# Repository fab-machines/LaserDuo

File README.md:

<div align="center"><h1 style="font-family: courier;" align="center">LaserDuo</h1></div>

<div align="center"></div>
<div align="center"><i>Open Source Dual Laser Cutter</i></div>

Premises
--
We dream in a future of freedom, where open source hardware and [Fab Labs](https://fablabs.io/) enable people to fully understand how to make things they need, and where decentralized local production is customized to impact the surrounding community. Believing that empowering the user with knowledge about how to make machines, LaserDuo wants to give to the world a powerful open source tool, to lasercut (almost) any material. And, together with [BigFDM](https://github.com/fab-machines/BigFDM), this is one of the first steps in developing other machines sharing the same philosophy.

LaserDuo
--
LaserDuo is an open source laser cutter having two different laser sources. Using a 130W CO2 and a 75W YAG lasers, LaserDuo can work with a wide range of materials such as wood and metals.

Taking advantage of what we have learned in [Fab Academy](https://fabacademy.org/), LaserDuo has been developed using standard [Fab Lab equipment](https://docs.google.com/spreadsheets/d/1U-jcBWOJEjBT5A0N84IUubtcHKMEMtndQPLCkZCkVsU/pub?single=true&gid=0&output=html) and [techniques](http://fab.academany.org/2019/schedule.html) plus a membrane press machine to bend the aluminum parts. LaserDuo was developed at [Fab Lab Kamp-Linfort](https://fablab.hochschule-rhein-waal.de/about-us) by Daniele Ingrassia. Reversing the consumer process, where knowledge and building of machines stays inside a black box managed by companies, LaserDuo brings the advantages of an open source development:

- full awareness about how the machine works
- reproducible design
- possibility to customize the machine and/or to build new ones
- built as much as possible with local materials
- local self-fixing and self-production of the machine parts
- community can use and improve the design
- cheap alternative to large scale 3D printers
- use LaserDuo as tool to produce other open source machines

Developed and built in a Fab Lab as multipurpose machine, LaserDuo allows to access the laser cutting technology at lower price in comparison to similar machines available on the market. Especially considering the possibility to work with metals. The open source design allows the user to fix the machine by himself, and to be aware of the process in a way that he can use it to reproduce the machine or parts for it. Being a challenging project from several aspects, such as size of the working area, Z-axis, speed, resolution and the dual laser, it also offers additional features like an integrated PC to control the machine and launch jobs, air assist, solid aluminum bodywork.

**LaserDuo specifications**:

- **1500mm x 1000mm** cutting area
- **500mm Z axis**
- **dual laser source**
- **130W CO2** laser
- **75W YAG** laser
- **800mm/s** maximum speed
- **Nema 24** stepper motors
- **air assist**
- integrated **tablet** for machine control
- **1000DPI or 0.0254mm** resolution
- open source **satshakit biards** for machine control
- dedicated sealed **exhaust chamber**
- **certified laser protective window**
- **safety features** emergency switch, windows interlock
- **fully enclosed 100% aluminum housing**
- dimensions: 2250mm x 2100mm x 1500mm

Machine design
--

The overall project has been designed by following a bottom-up approach, where the first step was to make a single machine axis. Every step focused on developing a single machine section, designing and constraining it according to the previous steps and machine features. You can consider this like being almost blind about the next step, until the current one has been assessed as able to work properly. It is therefore for me still astonishing the complete transition to the final machine look, generated by the chaining of the dependencies of several design steps.

X and Y stages
--

As many other laser cutters, also the stages of LaserDuo have been designed to be light and fast. Linear rails together with CNC milled POM and aluminium profiles have been used. To be noticed this step took a lot time, especially during the assembly to ensure the correct squareness of the frame and the perpendicularity of the axis. Both X and Y axis are moved by Nema 24 motors.

Z Axis
--

I always had something to do with lasers having Z axis, before learning that some chinese laser don’t have it. Therefore for me was quite normal to consider to have it. However I had a long reasoning about the justification of the extra costs vs the possible benefits. Then I had the idea to eventually make a 3D printer as a possible upgrade for LaserDuo, while considering that I still needed to find a solution to properly take the focus by moving the lens up and down. That convinced me to add it. The Z axis consist of 4 lead-screws, supported by ball bearings and moved a closed loop belt. The frame has been designed in a way to fit the Z axis inside and to have the machine high enough to be on wheels.

Inner enclousure
--

Designed on purpose to shield the laser focusing area and to make the fumes having a certain flow towards the exhaust system, the inner enclosure consists of CNC milled 1.5mm anodized aluminium sheets. There are vents both in the front and the back, allowing fresh air to come from outside, cool the cutting area, and be exhausted through a sealed box.

<br><br><br>

Housing
--

The housing completely encloses the machine, while keeping 3 exhaust tubes in the back and some ultrathin air intakes. The design uses curves to allow the feet to fit when coming close to the machine, and as well to save material. Laser, exhaust, electronics and optics are located in different areas, accessible by removing a specific panel for maintenance.

<br><br><br>

<br><br><br>

Electronics
--
The electronics of LaserDuo consists of a set of fabbable electronics, derived from the original **[satshakit](https://github.com/satshakit)** board and **[satstep](https://github.com/satstep)** stepper drivers. Following the used boards and their role in LaserDuo.<br>

**[satshakit-mega](https://github.com/fab-machines/LaserDuo/tree/master/electronics/satshakit-mega)**

Based on the [ATMega2560](https://www.microchip.com/wwwproducts/en/ATmega2560), this board provides the necessary microcontroller hardware to manage LaserDuo dual laser logic and additional sensors. Furthermore integrates an USB-to-Serial converter and USB port. Developed as general purpose board, not all the pins will be used. In the future this board will be a custom made solution for LaserDuo. Link to the original [repo](https://github.com/satshakit/satshakit-mega).

---------

**[satshakit-grbl](https://github.com/fab-machines/LaserDuo/tree/master/electronics/satshakit-grbl)**

Used to run **[GRBL 1.1](https://github.com/gnea/grbl)** in laser mode, satshakit-grbl is based on the ATMega328p and as well integrates nise filtering for the endstops. Link to the original repo [satshakit-grbl](https://github.com/satshakit/satshakit-grbl)

---------

**[satstep6600](https://github.com/fab-machines/LaserDuo/tree/master/electronics/satstep6600)**

Proved to have a robust design by being used in **[LaserDuo](http://laserduo.com/)** for more than a year, the satstep6600 is the stepper driver used to move the NEMA 24. Based on the Toshiba [TB6600HG](http://www.massmind.org/images/massmind/TB6600HG_datasheet.pdf) it can give up to 4.5A per coil to a single motor, whereas the NEMA 24 used will take a maximum of 4A. Link to the original [repo](https://github.com/satstep/satstep6600).

---------

Summary of the needed boards:

- 1 x satshakit-mega
- 1 x satshakit-grbl
- 3 x satstep6600

To power all this electronics, and to control the laser sources the following additional electronics is needed:

- 15A 24V power supply
- CO2 power supply (~40KV)
- YAG power supply

Make your own LaserDuo
--

LaserDuo is made by using a mix of fabricated and ready-made parts. The ready-made parts are selected to be as common/standard as possible, to make the sourcing of them easy in many countries. For both the raw materials needed for the fabricated parts, and the ready-made parts, refer to the Bill-of-Material for details: **[LaserDuo BOM](https://github.com/fab-machines/LaserDuo/raw/master/docs/LaserDuo%20BOM.pdf)**

The fabrication of the parts mainly relays on standard [Fab Lab equipment](https://docs.google.com/spreadsheets/d/1U-jcBWOJEjBT5A0N84IUubtcHKMEMtndQPLCkZCkVsU/pub?single=true&gid=0&output=html) plus a membrane press machine. Below a list of the required tools and machines:

- C02 laser cutter:
 - able to cut 8mm POM
 - needed for POM parts and holders
- large format wood CNC machine:
 - ShopBot or similar, size 2500x1250mm
 - to machine the POM parts (X, Y, Z, axis)
 - to machine the Aluminum parts (inner enclousure, housing)
- 3D printer:
 - a medium sized one (50x50x50cm)
 - to print the inner housing parts 
- Desktop format CNC machine:
 - Roland MDX50/MDX20/SRM20 or similar small machine (as well the cheap chinese ones)
 - to produce the required PCBs
- standard set of tools:
 - spanner key set
 - hex key set
 - DIN 875
 - calipers
 - rulers
 - screwdriver set
 - player set (grabber/cutter etc..)
 - clamps
 - rubber hummers
- membrane press machine
 - to bend the housing parts  

Both fabricated and ready-made parts have been modeled inside the **[LaserDuo Fusion 360 3D model](https://github.com/fab-machines/LaserDuo/raw/master/cad/LaserDuo.f3d)**. Using Fusion is possible to export/prepare the parts for production in the following ways:

- right click save as STL, on a body that needs to be 3D printed
- use the built-in Fusion CAM processor for the machined parts
- project on a surface, and then right click export as DXF, for laser cutting
 
For more details about the tools and once you have all the fabricated and ready-made parts parts available, refer to the for step-by-step assembly instructions and tips: **[LaserDuo Building Manual](https://github.com/fab-machines/LaserDuo/raw/master/docs/LaserDuo%20building%20manual.pdf)** 

LaserDuo requires different fabbable PCBs to work. Below the download links for the eagle files that you use to fabricate them:

- **[satshakit-mega schematic](https://raw.githubusercontent.com/fab-machines/LaserDuo/master/electronics/satshakit-mega/satshakit-mega.sch)**, **[satshakit-mega board](https://raw.githubusercontent.com/fab-machines/LaserDuo/master/electronics/satshakit-mega/satshakit-mega.brd)**

- **[satstep6600 schematic](https://github.com/fab-machines/LaserDuo/raw/master/electronics/satstep6600/satstep6600.sch)**, **[satstep6600 board](https://github.com/fab-machines/LaserDuo/raw/master/electronics/satstep6600/satstep6600.brd)**

- **[satshakit-grbl schematic](https://github.com/fab-machines/LaserDuo/raw/master/electronics/satshakit-grbl/satshakit-grbl.sch)**, **[satshakit-grbl board](https://github.com/fab-machines/LaserDuo/raw/master/electronics/satshakit-grbl/satshakit-grbl.brd)**

Media
--
**LaserDuo Videos**

**How to Make LaserDuo: Hamburg Workshop at [Open Lab](http://openlab-hamburg.de/startpage/)**

<br><br><br>

**LaserDuo pictures**

Author
--

The author of BigFDM is:

- **Daniele Ingrassia, daniele@inmachines.net**
- **[InMachines Ingrassia GmbH](https://www.inmachines.net/)**

Donations
--

Our dream is to have impact by making **open source machines digitally available and locally produced anywhere in world**. We plan to open a dedicated Fab Lab to foster open machine building and digital fabrication research. Practically several tasks and many expensens have to be sustained to give this dream the chance to have a future. Such as the renting of a proper space, the making/purchasing of proper equipment, the sustainability of our work and lifes. If you share this mindset and BigFDM is useful to you, please help us to make this dream a reality by donating your support:

Acknowledgements
--

**Thanks:**<br>
<br>
**[Fablab Kamp-Lintfort](https://fablab.hochschule-rhein-waal.de/)**<br />
Hochschule Rhein-Waal<br/>
Friedrich-Heinrich-Allee 25<br/>
47475 Kamp-Lintfort - Germany<br/>
[https://fablab.hochschule-rhein-waal.de/about-us](https://fablab.hochschule-rhein-waal.de/about-us)<br/>
[fablab@hochschule-rhein-waal.de](fablab@hochschule-rhein-waal.de)

Technical Help by **[Ahmed B. Abdellatif](http://archive.fabacademy.org/fabacademy2017/fablabkamplintfort/students/391/index.html)**<br/>
Logo Design by **Jana-Lina Berkenbusch**<br/>
Photographs by **Christian Spieß**<br/>
Website development by **Emir Rustamov**<br/>

****

License
-- 
LaserDuo, its hardware design, CAD, BOM, settings and relative files are are released under the following open source license:

- CERN Open Hardware Licence Version 2 Weakly Reciprocal - **[CERN-OHL-W](LICENSE_CERN_OHL_W_V2.txt)**

Note
--

This documentation will be continuously improved as soon there are updates and/or improvements on the machine.

Disclaimer  
--

<div class="align-justify">
This hardware/software is provided "as is", and you use the hardware/software at your own risk. Under no circumstances shall any author be liable for direct, indirect, special, incidental, or consequential damages resulting from the use, misuse, or inability to use this hardware/software, even if the authors have been advised of the possibility of such damages.</div>

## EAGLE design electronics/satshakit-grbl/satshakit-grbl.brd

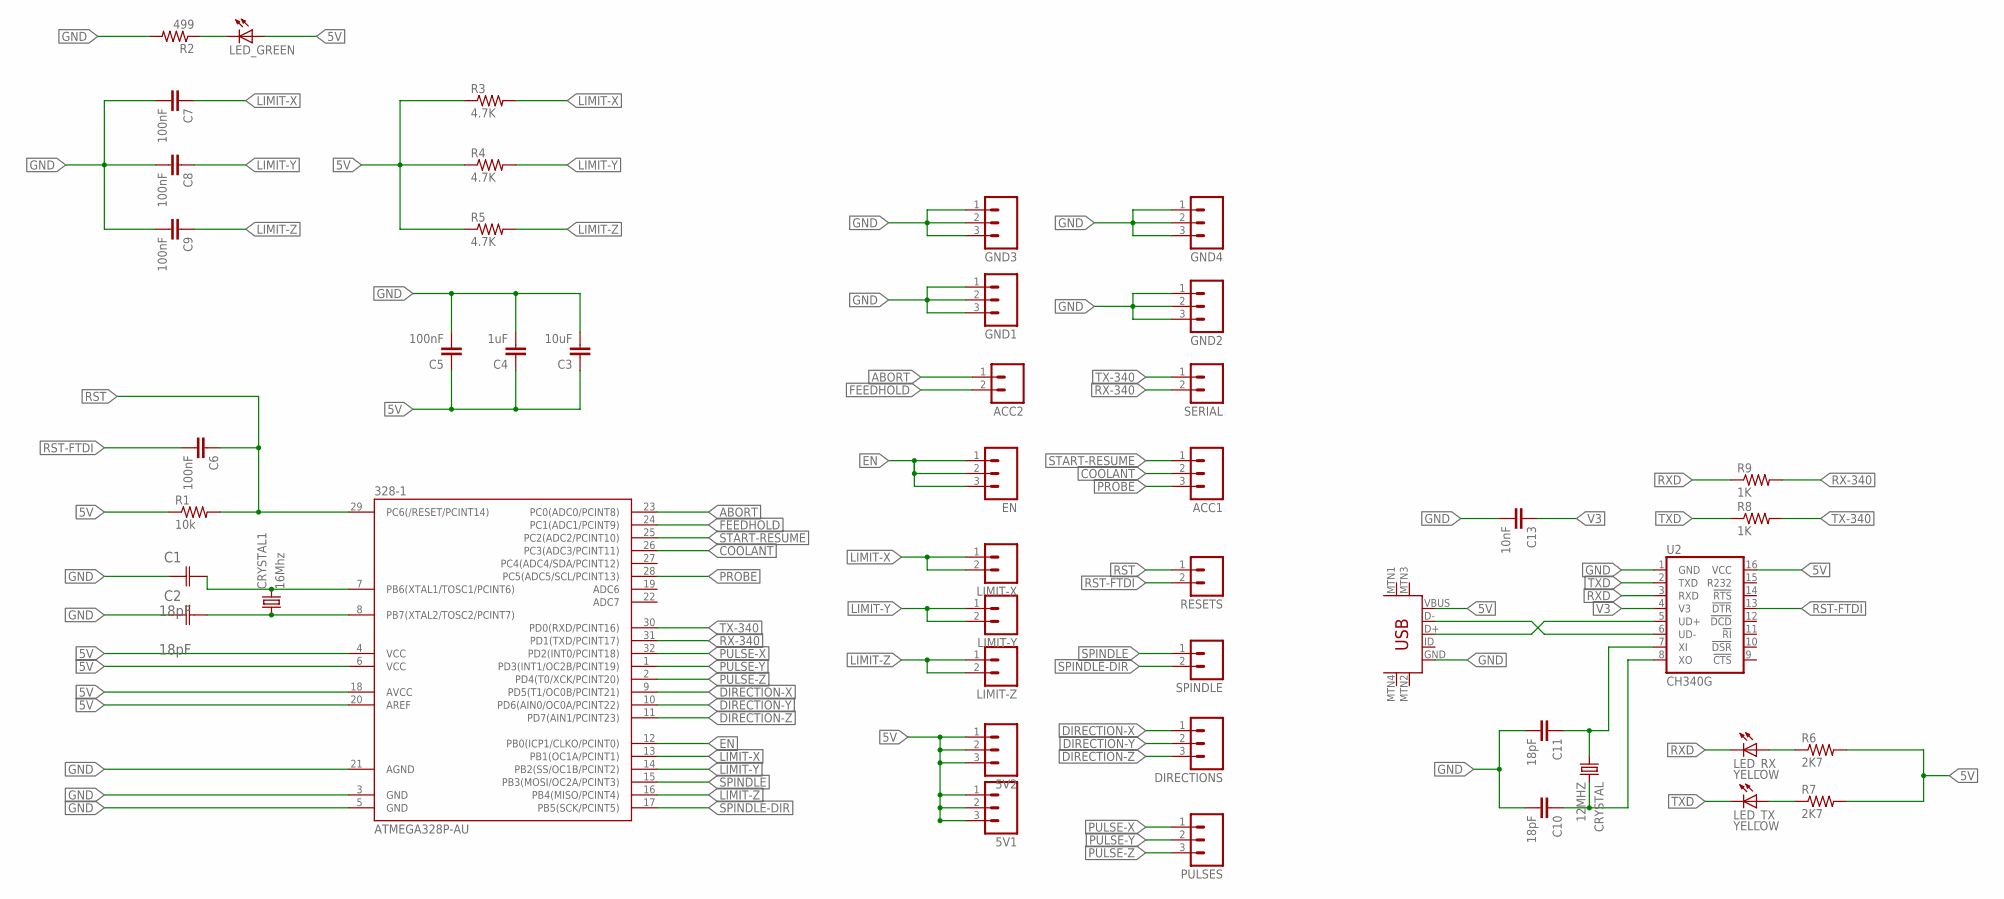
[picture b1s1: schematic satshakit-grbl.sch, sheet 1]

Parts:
5V1, 5V2: M03; 03P
328-1: ATMEGA328P-AU; TQFP32-08
ACC1: M03; 03P
ACC2: M02; 02P
C1, C2: 18pF; CAPC3216X178N
C3: 10uF; 1206
C4: 1uF; 1206
C5, C6, C7, C8, C9: 100nF; 1206
C10, C11: 18pF; 1206
C13: 10nF; 1206
CRYSTAL: 12MHZ; CSM-7X-DU
CRYSTAL1: 16Mhz; CSM-7X-DU
DIRECTIONS: M03; 03P
EN: M03; 03P
GND1, GND2, GND3, GND4: M03; 03P
LED_GREEN: LED1206; 1206
LED_RX: YELLOW; LED1206
LED_TX: YELLOW; LED1206
LIMIT-X: M02; 02P
LIMIT-Y: M02; 02P
LIMIT-Z: M02; 02P
PULSES: M03; 03P
R1: 10k; 1206
R2: 499; 1206
R3, R4, R5: 4.7K; 1206
R6, R7: 2K7; R1206
R8, R9: 1K; R1206
RESETS: M02; 02P
SERIAL: M02; 02P
SPINDLE: M02; 02P
U2: CH340G; SO016
U$7: USB-MINIB-5PIN; USB-MINIB

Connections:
5V: 5V1.1, 5V1.2, 5V1.3, 5V2.1, 5V2.2, 5V2.3, 328-1.4 (VCC), 328-1.6 (VCC), 328-1.18 (AVCC), 328-1.20 (AREF), C3.1, C4.1, C5.1, LED_GREEN.1 (A), R1.1, R3.1, R4.1, R5.1, R6.2, R7.2, U2.16 (VCC), U$7.VBUS
ABORT: 328-1.23 (PC0(ADC0/PCINT8)), ACC2.1
COOLANT: 328-1.26 (PC3(ADC3/PCINT11)), ACC1.2
DIRECTION-X: 328-1.9 (PD5(T1/OC0B/PCINT21)), DIRECTIONS.1
DIRECTION-Y: 328-1.10 (PD6(AIN0/OC0A/PCINT22)), DIRECTIONS.2
DIRECTION-Z: 328-1.11 (PD7(AIN1/PCINT23)), DIRECTIONS.3
EN: 328-1.12 (PB0(ICP1/CLKO/PCINT0)), EN.1, EN.2, EN.3
FEEDHOLD: 328-1.24 (PC1(ADC1/PCINT9)), ACC2.2
GND: 328-1.3 (GND), 328-1.5 (GND), 328-1.21 (AGND), C1.1 (C1), C2.1 (C1), C3.2, C4.2, C5.2, C7.2, C8.2, C9.2, C10.2, C11.2, C13.2, GND1.1, GND1.2, GND1.3, GND2.1, GND2.2, GND2.3, GND3.1, GND3.2, GND3.3, GND4.1, GND4.2, GND4.3, R2.2, U2.1 (GND), U$7.GND
LIMIT-X: 328-1.13 (PB1(OC1A/PCINT1)), C7.1, LIMIT-X.1, LIMIT-X.2, R3.2
LIMIT-Y: 328-1.14 (PB2(SS/OC1B/PCINT2)), C8.1, LIMIT-Y.1, LIMIT-Y.2, R4.2
LIMIT-Z: 328-1.16 (PB4(MISO/PCINT4)), C9.1, LIMIT-Z.1, LIMIT-Z.2, R5.2
unnamed: U2.5 (UD+), U$7.D+
unnamed: 328-1.7 (PB6(XTAL1/TOSC1/PCINT6)), C1.2 (C2), CRYSTAL1.2
unnamed: U2.6 (UD-), U$7.D-
unnamed: LED_RX.1 (A), R6.1
unnamed: LED_TX.1 (A), R7.1
unnamed: 328-1.8 (PB7(XTAL2/TOSC2/PCINT7)), C2.2 (C2), CRYSTAL1.1
unnamed: LED_GREEN.2 (C), R2.1
OSC_IN: C10.1, CRYSTAL.2, U2.8 (XO)
OSC_OUT: C11.1, CRYSTAL.1, U2.7 (XI)
PROBE: 328-1.28 (PC5(ADC5/SCL/PCINT13)), ACC1.3
PULSE-X: 328-1.32 (PD2(INT0/PCINT18)), PULSES.1
PULSE-Y: 328-1.1 (PD3(INT1/OC2B/PCINT19)), PULSES.2
PULSE-Z: 328-1.2 (PD4(T0/XCK/PCINT20)), PULSES.3
RST: 328-1.29 (PC6(/RESET/PCINT14)), C6.1, R1.2, RESETS.1
RST-FTDI: C6.2, RESETS.2, U2.13 (!DTR)
RX-340: 328-1.31 (PD1(TXD/PCINT17)), R9.2, SERIAL.2
RXD: LED_RX.2 (C), R9.1, U2.3 (RXD)
SPINDLE: 328-1.15 (PB3(MOSI/OC2A/PCINT3)), SPINDLE.1
SPINDLE-DIR: 328-1.17 (PB5(SCK/PCINT5)), SPINDLE.2
START-RESUME: 328-1.25 (PC2(ADC2/PCINT10)), ACC1.1
TX-340: 328-1.30 (PD0(RXD/PCINT16)), R8.2, SERIAL.1
TXD: LED_TX.2 (C), R8.1, U2.2 (TXD)
V3: C13.1, U2.4 (V3)

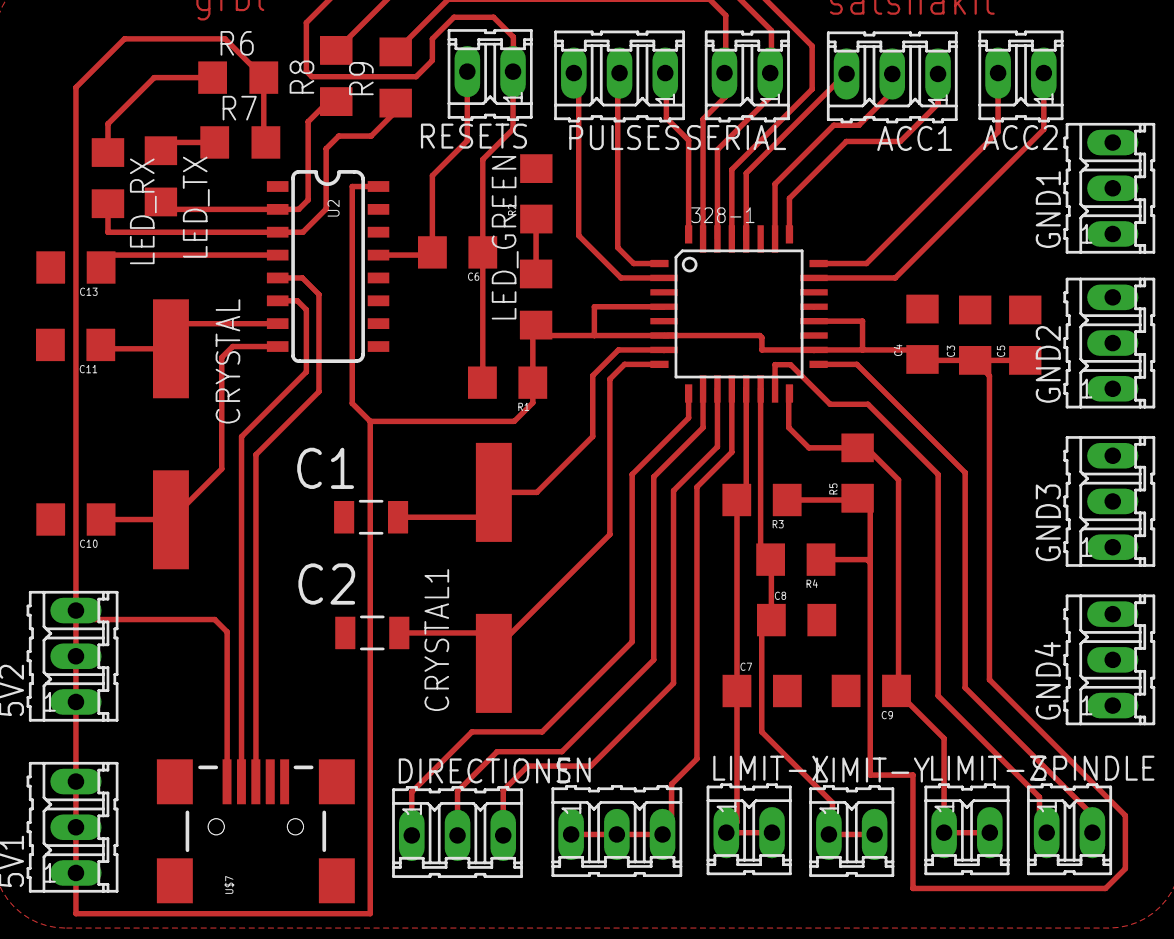
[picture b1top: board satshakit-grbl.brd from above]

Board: 2 copper layers, 46 parts (0 on the bottom side), 35 nets.

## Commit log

2019-08-10 first LaserDuo commit
2019-08-10 fixed links

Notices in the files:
parts and their libraries:
01_SparkFun: Licensing: CC v3.0 Share-Alike You are welcome to use this library for commercial purposes.
SparkFun-DigitalIC: Licensing: Creative Commons ShareAlike 4.0 International - https://creativecommons.org/licenses/by-sa/4.0
